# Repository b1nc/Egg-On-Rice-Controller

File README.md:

# Egg On Rice Controller
 Micro hitbox-style controller for arcade games. Utilizes the Brook UFB.
 Heavily inspired by the "Mille-feuille" by Pomeran. https://pomegd.booth.pm/items/2685530
-

**Why is it called "Egg On Rice"? I love egg on rice hell yeah.**

- *Feel free to modify the files to your needs and specifications but credit me for the original files, please.*

- *All of the parts used will be linked or named in the materials.txt file.*

- *The switch footprints were made with Kailh Choc v1 switches in mind.*

- *The keycaps may be too low and sit flush with the top acrylic panel. Please modify either the stem length or the blocker length to your needs.*

- *No RGB because it hurts my eyes. (I'm just too lazy to implement it.)*

 USB Type-C Connection because we live in 2020s A.D, not 2020s B.C. Micro USBs should just die.  
 (However, USB-Cs are a pain to hand solder, but again, I'm bad at soldering.)

 6 tactile push switches for menu navigations.  
 (I don't even own a PS4 or Xbox, what do these buttons even do.)  
 From left to right (in playing position): Home, Touchpad, LSB (huh), RSB (what), Share, Option (the only one I use).

 I couldn't find an M6 screw feet without sacrificing the overall thickness of the board, so I made the thing feetless.  
 (The back does kinda look clean, though.)

 I'm sorry for my bad photography skills.  
   
 Here's a picture of the PCB using a PCB viewer.

 Buttons.

## Design Process ##  
Started with a drawing of the basic outline and layout for the PCB (switches, resistors, push buttons, and UFB).  

Then exported the sketch as a dxf file and ported it into KiCad for component alignments.

The schematics for this PCB board are extremely simple. The only hard part was failing to find a UFB footprint and having to make my own. (UFB footprint is contained in this project and free to use, while it might not look good, it gets the job done.)

After routing the board, edge cuts are added for M6 screw holes and artwork. (Feel free to edit the files to implement your personal artwork.)

Panel 1 and 2 are adjusted to fit with each other. If artwork isn't a concern, the bottom panel can also be used for the top panel to reduce cutting costs.

Cap dimensions are made to fit almost flush with the top panels while the stems are made according to the Kailh Choc v1 datasheet.

## Building Instructions ##
All of the files needed are in this repo.

In the PCB folder, there's a Gerber.zip folder within the Gerber folder. Use this for PCB manufacturing.  
(I used JLCPCB for PCB prototyping.)  
  
In the Acrylic Layers folder, check which set of panels you want to use and use the dxf files for cutting.  
(Please refer to the drawing and readme for panel thickness and amount.)  
(I used SendCutSend laser cutting service for all my acrylic panels.)  
  
The button caps are made for Kailh Choc v1 switches and are in the Button Keycaps folder with both step and stl files available.  
(I don't plan on making keycaps for MX stems, but feel free to modify the files.)  
(Sculpteo has amazing prices for small 3D prints like these caps.)  

PCB assembly should be pretty straightforward. Two 5.1 kOhm resistors on the top right corner, 6 push tact. switches on the top left, and a USB Type-C connector.  
(USB Type-C connector was kind of tricky for me to solder, so I used a reflow station, instead.)  
(All components are through-hole except for the USB-C.)  
  
The UFB is connected by headers, and you should only need to solder the 2x10 button controls and the power joints.  
(You will need to desolder the UFB pin connectors and the USB B connector first.)  
(I recommend soldering the GND pins for the 1x20 pins as well so the UFB sits flush and stable.)  

## Have fun making your very own hitbox-styled compact controller! :^) ##

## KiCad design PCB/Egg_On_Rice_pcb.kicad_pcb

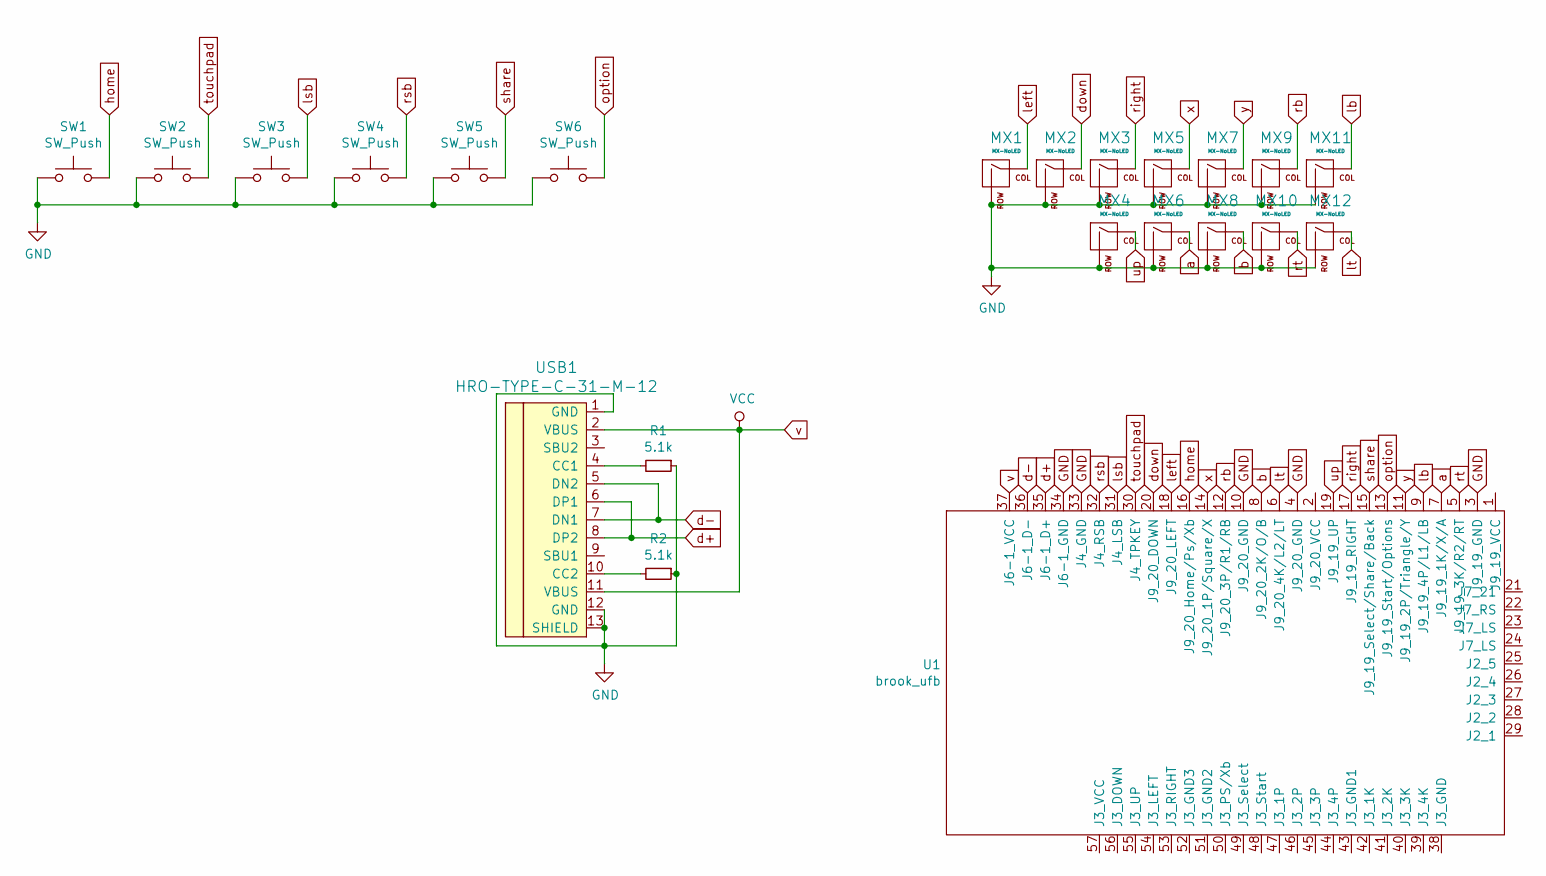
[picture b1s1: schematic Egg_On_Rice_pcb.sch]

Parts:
MX1, MX2, MX3, MX4, MX5, MX6, MX7, MX8, MX9, MX10, MX11, MX12: MX-NoLED; KailhChoc-1U
R1, R2: 5.1k; R_Axial_DIN0207_L6.3mm_D2.5mm_P10.16mm_Horizontal
SW1, SW2, SW3, SW4, SW5, SW6: SW_Push; spst_no_lph_6mm_6mm
U1: brook_ufb; Brook_Universal_Fighting_Board
USB1: HRO-TYPE-C-31-M-12

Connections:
GND: MX1.2 (ROW), MX2.2 (ROW), MX3.2 (ROW), MX4.2 (ROW), MX5.2 (ROW), MX6.2 (ROW), MX7.2 (ROW), MX8.2 (ROW), MX9.2 (ROW), MX10.2 (ROW), MX11.2 (ROW), MX12.2 (ROW), R1.1, R2.1, SW1.1, SW2.1, SW3.1, SW4.1, SW5.1, SW6.1, U1.3 (J9_19_GND), U1.4 (J9_20_GND), U1.10 (J9_20_GND), U1.33 (J4_GND), U1.34 (J6-1_GND), USB1.1 (GND), USB1.12 (GND), USB1.13 (SHIELD)
unnamed: R1.2, USB1.4 (CC1)
unnamed: R2.2, USB1.10 (CC2)
a: MX6.1 (COL), U1.7 (J9_19_1K/X/A)
b: MX8.1 (COL), U1.8 (J9_20_2K/O/B)
d+: U1.35 (J6-1_D+), USB1.6 (DP1), USB1.8 (DP2)
d-: U1.36 (J6-1_D-), USB1.5 (DN2), USB1.7 (DN1)
down: MX2.1 (COL), U1.20 (J9_20_DOWN)
home: SW1.2, U1.16 (J9_20_Home/Ps/Xb)
lb: MX11.1 (COL), U1.9 (J9_19_4P/L1/LB)
left: MX1.1 (COL), U1.18 (J9_20_LEFT)
lsb: SW3.2, U1.31 (J4_LSB)
lt: MX12.1 (COL), U1.6 (J9_20_4K/L2/LT)
option: SW6.2, U1.13 (J9_19_Start/Options)
rb: MX9.1 (COL), U1.12 (J9_20_3P/R1/RB)
right: MX3.1 (COL), U1.17 (J9_19_RIGHT)
rsb: SW4.2, U1.32 (J4_RSB)
rt: MX10.1 (COL), U1.5 (J9_19_3K/R2/RT)
share: SW5.2, U1.15 (J9_19_Select/Share/Back)
touchpad: SW2.2, U1.30 (J4_TPKEY)
up: MX4.1 (COL), U1.19 (J9_19_UP)
v: U1.37 (J6-1_VCC), USB1.2 (VBUS), USB1.11 (VBUS)
x: MX5.1 (COL), U1.14 (J9_20_1P/Square/X)
y: MX7.1 (COL), U1.11 (J9_19_2P/Triangle/Y)

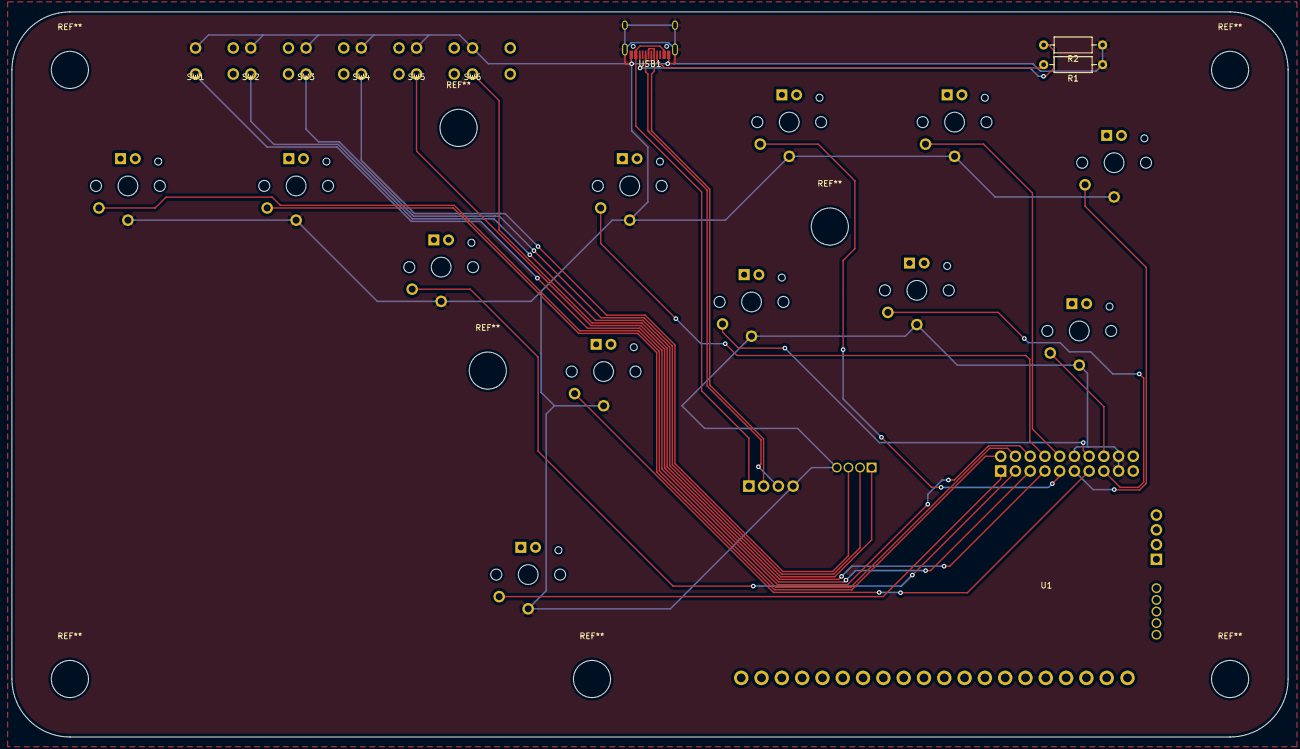
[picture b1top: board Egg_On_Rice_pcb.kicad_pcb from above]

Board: 2 copper layers, 220.0 x 125.0 mm, 22 parts (0 on the bottom side), 24 nets.

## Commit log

2021-10-15 Added Images
2021-10-15 Added more images
2021-10-15 Added more additional images
2021-10-19 Update LICENSE
2024-08-28 Update README.md
    Removed/replaced to make the wording more clear. Overall idea should be the same.
